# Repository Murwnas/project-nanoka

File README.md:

# project-nanoka

Project Nanoka is a Raspberry Pi Pico based audio output/input board. It exposes two audio terminals (input and output) as well as seven general-purposes input/output lines for external control. 

The PCB can be powered either through the Raspberry Pi's USB port, or through the power terminal. This requires a power module, which is also hosted on GitHub.

This version has several improvements over v1.2:
1. SD card support. It no longer relies on the small flash chip, which is very limited in space, especially when CircuitPython is used for firmware.
2. A Texas Instruments i2s DAC instead of lower quality PWM audio.
3. Stereo audio! Both on input and output
4. Ditches the noisy relay for an analogue switch IC.
5. Mostly SMD components, which makes the board cheaper.

Consequently, the SMD components makes this much harder to hand-solder than the previous version. The old version is still capable enough (deployed in a real environment right now) so if soldering skills and/or equipment is limited, the older version might be preferable over this. 

## Real reproduction (Aivon + DigiKey)

Known issues:
1. Piezo doesn't work. R6 pulls down the line too much, preventing the Pico GPIO from driving its gate properly. This can probably be fixed with a higher resistor value.
2. Missing trace to DAC's power pin. This can be band-aid fixed with a bodge wire (see picture).
3. Most SDIO drivers expect a D0+3 consecutive pin order. This has a D0-3 order. I was able to patch the no-OS-FatFS-SD-SDIO-SPI-RPi-Pico driver (great name, btw) to overcome this though.
4. Not the best SD routing. But it works fast enough for this project's purposes. Tested to perform with 9 MB/s read and 5.7 MB/s write speeds at 20 MHz.

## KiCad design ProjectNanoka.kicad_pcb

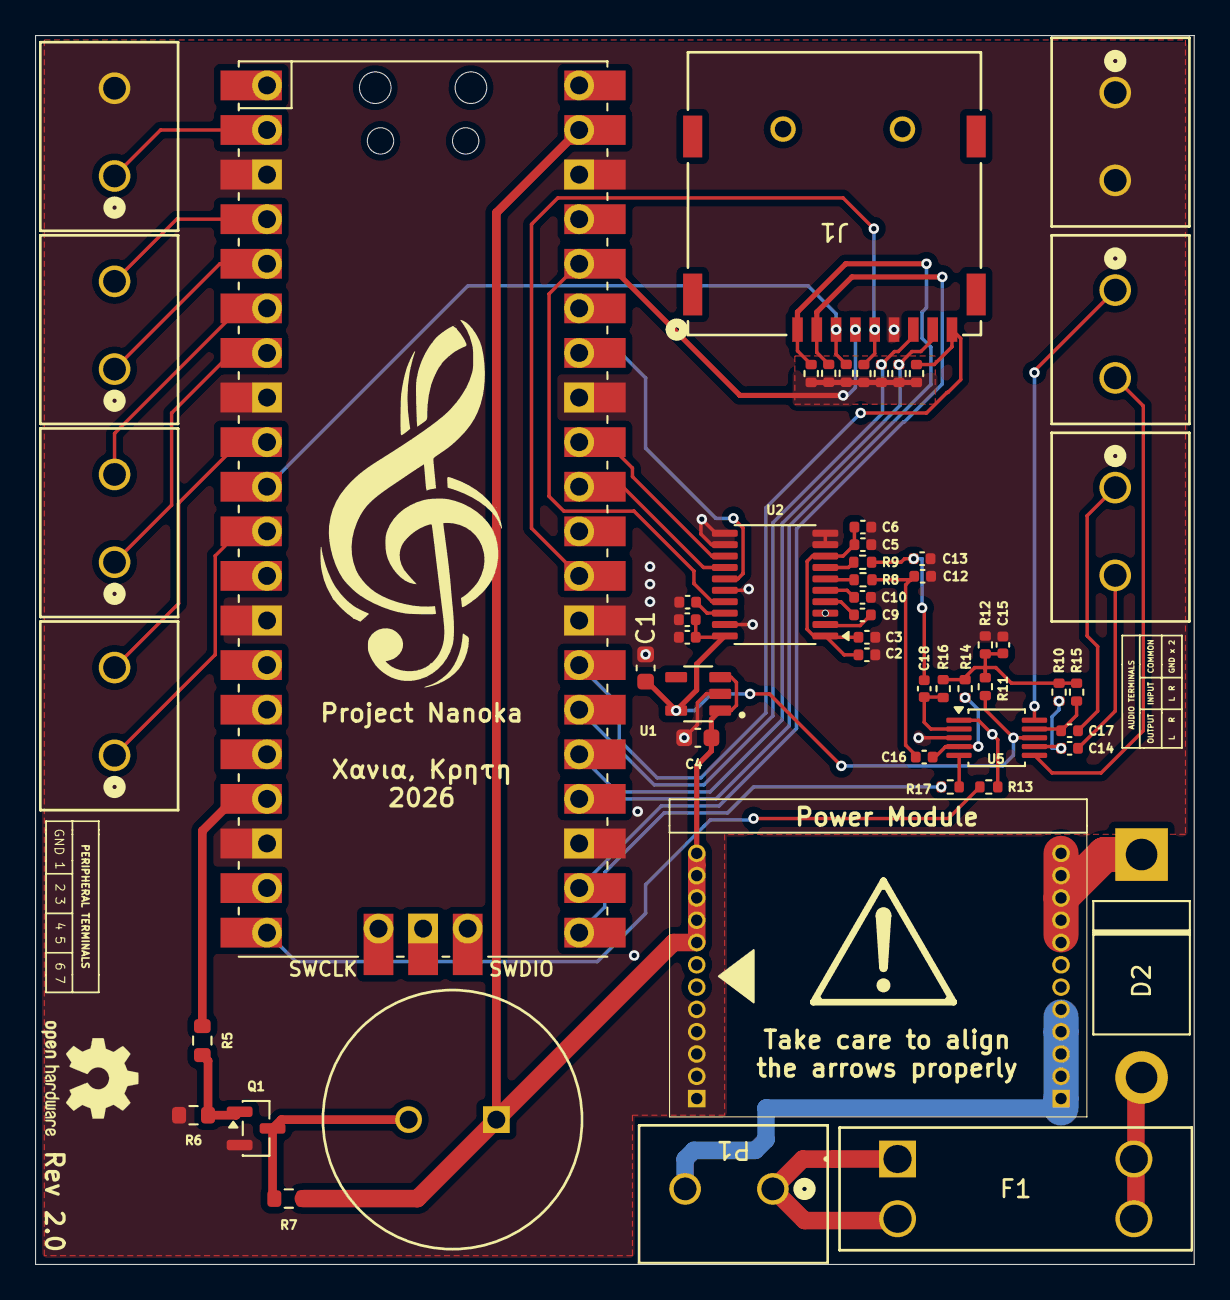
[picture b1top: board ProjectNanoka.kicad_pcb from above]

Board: 2 copper layers, 66.0 x 70.0 mm, 57 parts (0 on the bottom side), 49 nets.

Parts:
A1: RaspberryPi_Pico; RPi_Pico_SMD_TH
A_GND1: TERM; TERMINAL
A_IN1: TERM; TERMINAL
A_OUT1: TERM; TERMINAL
C1, C4: 1uf; C_0603_1608Metric
C2, C6, C8: 10u; C_0402_1005Metric
C3, C5, C7, C11: 100n; C_0402_1005Metric
C9, C10: 2.2u; C_0402_1005Metric
C12, C13: 2.2n; C_0402_1005Metric
C14, C16, C17, C18: 4.7uF; C_0402_1005Metric
C15: 1uF; C_0402_1005Metric
D2: 25A; P33_D5.4x7.5
F1: 1A; FUSE_HOLDER
GT1, GT2, GT3, GT4: TERM; TERMINAL
H1, H2: 1.27mm_12pin; PinHeader_1x12_P1.27mm_Vertical_Modded
J1: SD_SLOT
P1: TERM; TERMINAL
Q1: MMBT3904; SOT-23
R5, R7: 1k; R_0603_1608Metric
R6: 10k; R_0603_1608Metric
R8, R9: 270; R_0402_1005Metric
R10, R14, R15, R16: 100k; R_0402_1005Metric
R11, R12: 250k; R_0402_1005Metric
R13, R17: 2k; R_0402_1005Metric
R18, R19, R20, R21, R22, R23, R24: 47k; R_0402_1005Metric
U1: TLV70033DDCR; SOT95P280X110-5N
U2: PCM5101A; TSSOP-20_4.4x6.5mm_P0.65mm
U3: PS1440P02BT; PS1440P02BT_TDK
U5: TS5A23159DGS; TSSOP-10_3x3mm_P0.5mm

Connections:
1V65_VD: C15.1, R10.1, R11.1, R12.2, R14.2, R15.1, R16.2
3.3AS: C1.1, C7.2, C8.2, R11.2, U1.5 (OUT), U2.20 (DVDD), U5.8 (VCC)
3V3: A1.36 (3V3), C2.1, C3.1, C5.1, C6.1, J1.P4 (VDD), R18.2, R19.2, R20.2, R21.1, R22.1, R23.1, R24.1, U2.1 (CPVDD), U2.8 (AVDD), U2.17 (XSMT)
+5V: A1.39 (VSYS), C4.1, H1.8, H1.9, H1.10, H1.11, H1.12, R7.2, U1.1 (IN), U1.3 (EN), U3.1
/EAL: C14.2, R10.2, U5.7
/EAR: C17.2, R15.2, U5.9
/PAL: C16.1, R14.1, U5.4
/PAR: C18.1, R16.1, U5.2
AUDIO_OUT_LEFT: A_OUT1.2, U5.6
AUDIO_OUT_RIGHT: A_OUT1.1, U5.10
EXT_AUDIO_LEFT: A_IN1.2, C14.1
EXT_AUDIO_RIGHT: A_IN1.1, C17.1
GNDPWR: A1.3 (GND), A1.8 (GND), A1.13 (GND), A1.18 (GND), A1.23 (GND), A1.28 (GND), A1.33 (AGND), A1.38 (GND), A_GND1.1, A_GND1.2, C1.2, C2.2, C3.2, C4.2, C5.2, C6.2, C7.1, C8.1, C10.2, C11.2, C12.2, C13.2, C15.2, GT1.2, H1.1, H1.2, H1.3, H1.4, H1.5, J1.P6 (VSS), Q1.2 (E), R6.2, R12.1, U1.2 (GND), U2.3 (CPGND), U2.9 (AGND), U2.10 (DEMP), U2.11 (FLT), U2.12 (SCK), U2.16 (FMT), U2.19 (DGND), U5.3 (GND)
GP1: A1.2 (GPIO1), GT1.1
GP2: A1.4 (GPIO2), GT2.2
GP3: A1.5 (GPIO3), GT2.1
GP4: A1.6 (GPIO4), GT3.2
GP5: A1.7 (GPIO5), GT3.1
GP6: A1.9 (GPIO6), GT4.2
GP7: A1.11 (GPIO8), GT4.1
GPIO15: A1.20 (GPIO15), R13.2
GPIO16: A1.21 (GPIO16), R17.2
GPIO26: A1.31 (GPIO26_ADC0), U2.14 (DIN)
GPIO27: A1.32 (GPIO27_ADC1), U2.13 (BCK)
GPIO28: A1.34 (GPIO28_ADC2), U2.15 (LRCK)
unnamed: A1.17 (GPIO13), R5.1
unnamed: D2.2 (A), F1.3, F1.4
unnamed: D2.1 (K), H2.8, H2.9, H2.10, H2.11, H2.12
unnamed: H2.1, H2.2, H2.3, H2.4, H2.5, P1.2
unnamed: F1.1, F1.2, P1.1
unnamed: Q1.1 (B), R5.2, R6.1
unnamed: Q1.3 (C), R7.1, U3.2
unnamed: R13.1, U5.1
unnamed: R17.1, U5.5
unnamed: C9.2, U2.4 (CAPM)
unnamed: C9.1, U2.2 (CAPP)
unnamed: C11.1, U2.18 (LDOO)
unnamed: R8.1, U2.6 (OUTL)
unnamed: R9.1, U2.7 (OUTR)
unnamed: C10.1, U2.5 (VNEG)
PCM_AUDIO_L: C12.1, C16.2, R8.2
PCM_AUDIO_R: C13.1, C18.2, R9.2
SD_CD: A1.27 (GPIO21), J1.P9 (CD), R22.2
SD_CD/DAT3: A1.22 (GPIO17), J1.P2 (CD/DAT3), R20.1
SD_CLK: A1.29 (GPIO22), J1.P5 (CLK), R23.2
SD_CMD: A1.10 (GPIO7), J1.P3 (CMD), R18.1
SD_DAT0: A1.26 (GPIO20), J1.P7 (DAT0), R21.2
SD_DAT1: A1.25 (GPIO19), J1.P8 (DAT1), R24.2
SD_DAT2: A1.24 (GPIO18), J1.P1 (DAT2), R19.1

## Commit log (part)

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2025-08-26 Modified decoupling problem at layout
